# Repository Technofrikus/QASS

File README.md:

# QASS

QAZ-like for a BAE (Big Ass Enter) and 10u spacebar (7u+8u)

More pictures and infos at [Moinboards](https://moinboards.de/projects/qass/).
[Buildguide](https://moinboards.de/guides/guide-qass/).

There are three versions: normal, lowbar (Miao for FAK-Firmware) and lowbar (Gemini for QMK/Vial). The normal version has the spacebar on the normal PCB. The lowbar uses the PCB as a plate on the bottom row and adds a lower PCB.

- Only the lowbar version was tested and fully finished. Please check the normal version before ordering.
- Lowbar:
  - v1.0 is tested and works with MIAO. XIAO would work as well but the pads on the underside I wanted to use are not GPIOs but only for a special serial protocol. So they cant be used.
  - v1.1 is Untested, but I only made cosmetic changes, so should still work fine.
  - Quark-Works made a fork and changed the MCU to a [Gemini](https://keeb.supply/products/0xcb-gemini) (rp2040 zero compatible). Thanks! You can find it [here](https://github.com/quark-works/QASS-Zero/tree/main).
  - v1.2 Used the fork by Quarks as a basis. Removed a little mistake and made some cosmetic changes.
  - v1.3 the prvious version works, but the silkscreen of the diodes is not visible (orientation of diodes). Corrected this and changed the direction of one diode to be more consistent with the other ones around it.

The latest version has the lower spacebar. Break off the lower part of the PCB and put it under the bottom row. Add headers at the connection points.

## Case

The 3D-printable case files are included now (March 2025).
Can recommend making the plate from metal. Gives the build more weight and looks nice. Tested with brass and copper. Use the special version to make sure they will not warp during cutting (havent tested it without these, just a precaution).
Print recommendations included, see txt file. 

It is for the low-bar version only.

## Firmware
- FAK config and info can be found on [moinboards](https://moinboards.de/guides/guide-qass/#firmware-and-flashing) and here in the firmware folder.
- Vial/Qmk for the fork by Quark. Confirmed working.

## BOM

- [Miao MCU](https://keeb.supply/products/miao) (or [Gemini](https://keeb.supply/products/0xcb-gemini), if you use the Gemini-PCB
- 3mm high hotswap headers (2.54mm pitch) and pins (the holes in the PCB are bigger than usual, so only the plastic part of the headers is on the PCB)
- 20x BAV70 diodes

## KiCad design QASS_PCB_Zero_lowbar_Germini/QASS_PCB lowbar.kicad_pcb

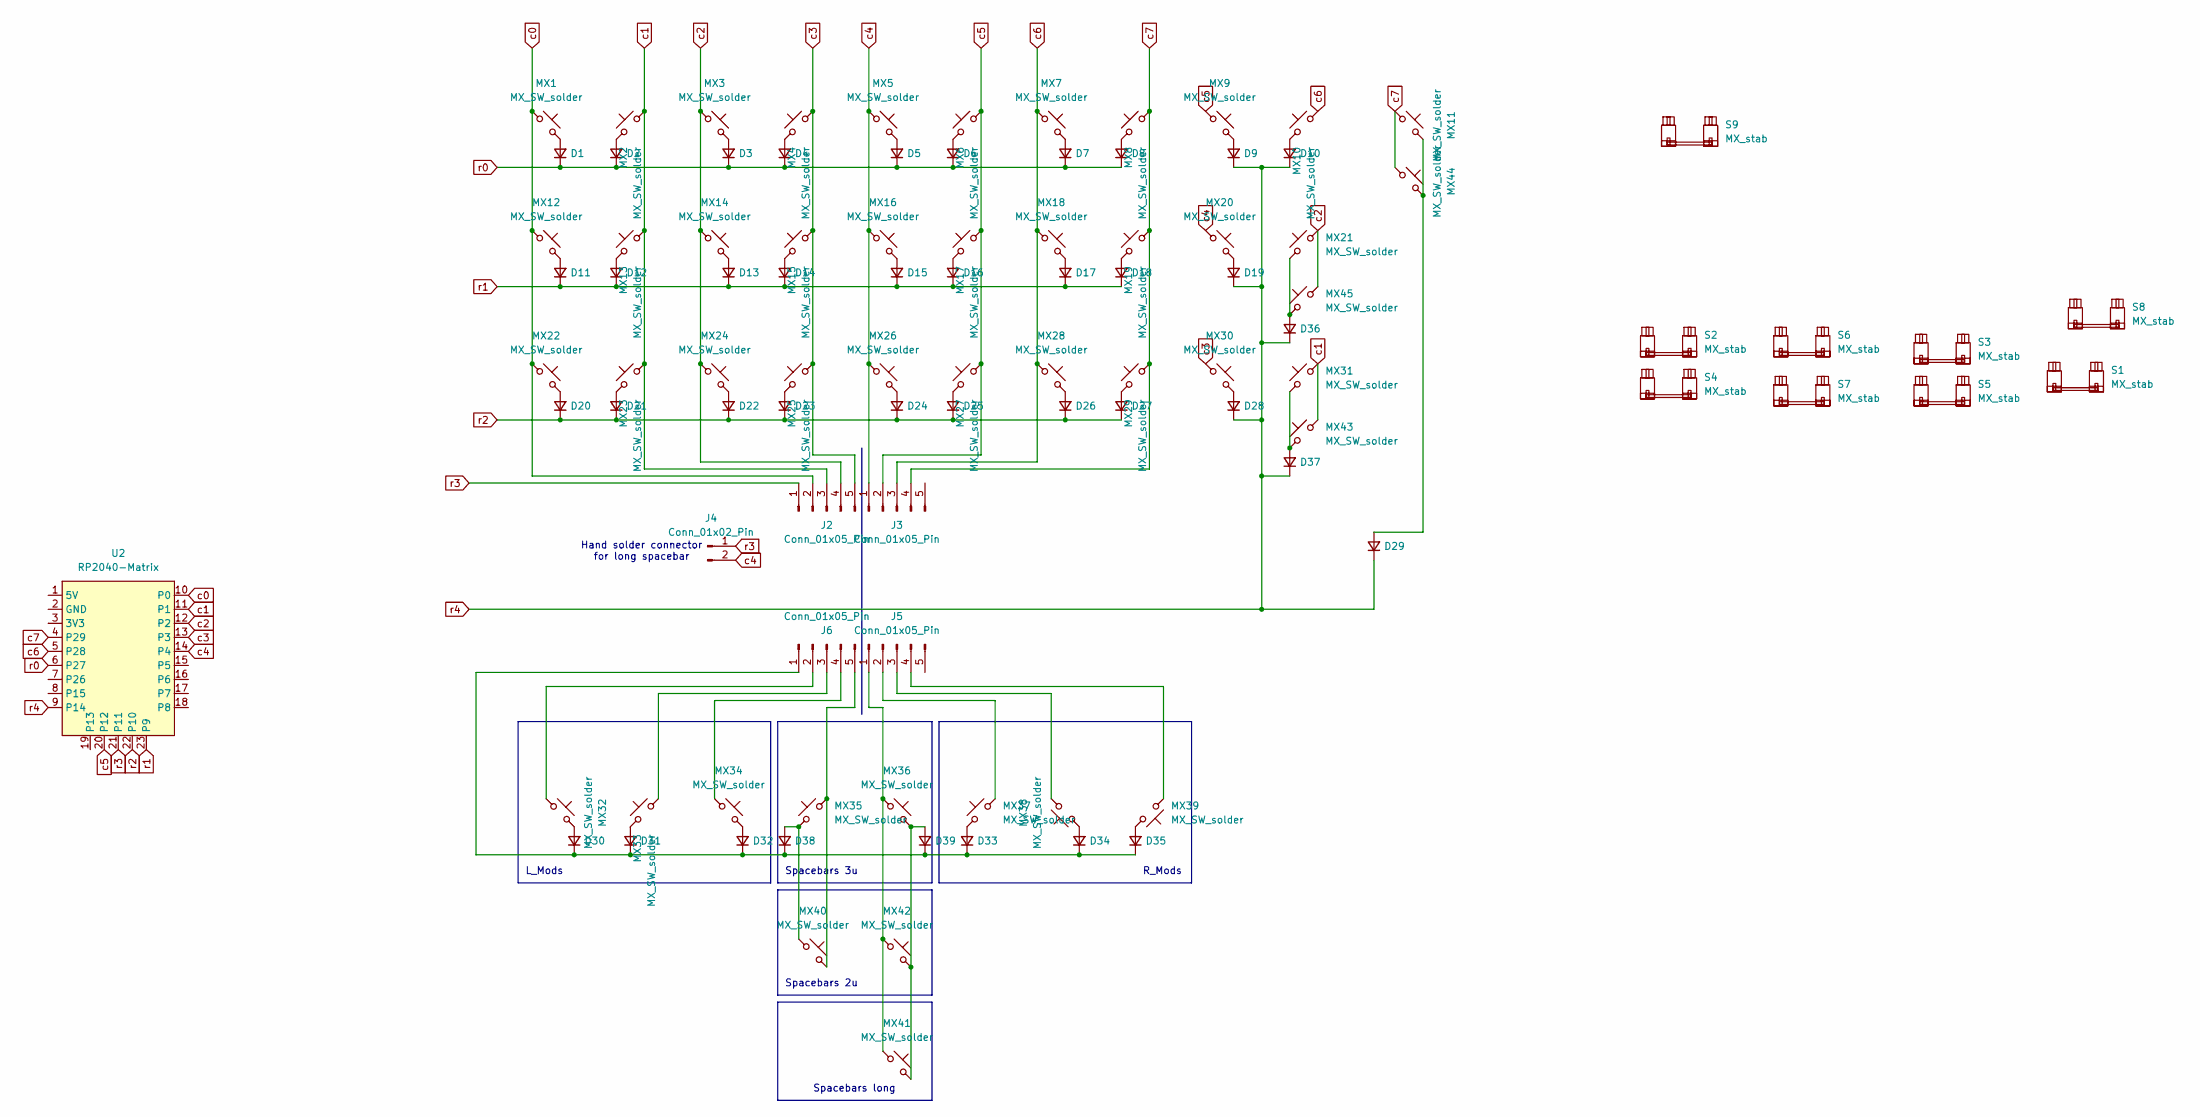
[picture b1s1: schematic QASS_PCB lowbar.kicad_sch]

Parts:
D1, D2, D3, D4, D5, D6, D7, D8, D9, D10, D11, D12, D13, D14, D15, D16, D17, D18, D19, D20, D21, D22, D23, D24, D25, D26, D27, D28, D29, D30, D31, D32, D33, D34, D35, D36, D37, D38, D39: 1n4148; Diode-dual
J2, J3, J5, J6: Conn_01x05_Pin; PinHeader_1x05_P2.54mm_Vertical
J4: Conn_01x02_Pin; PinHeader_1x02_P2.54mm_Vertical
MX1, MX2, MX3, MX4, MX5, MX6, MX7, MX8, MX9, MX10, MX13, MX14, MX15, MX16, MX17, MX18, MX19, MX20, MX21, MX23, MX24, MX25, MX26, MX27, MX28, MX29, MX30, MX32, MX33, MX34, MX35, MX36, MX37, MX38, MX39, MX40, MX41, MX42, MX43, MX45: MX_SW_solder; SW_MX_1u
MX11, MX44: MX_SW_solder; SW_MX_1.5u
MX12: MX_SW_solder; SW_MX_1.25u
MX22, MX31: MX_SW_solder; SW_MX_1.75u
S1: MX_stab; STAB_MX_2.25u
S2, S3: MX_stab; STAB_MX_3u
S4, S5: MX_stab; STAB_MX_2u
S6: MX_stab; STAB_MX_P_6u
S7: MX_stab; STAB_MX_P_10u
S8: MX_stab; STAB_MX_2.75u
S9: MX_stab; STAB_MX_P_ISO
U2: RP2040-Matrix; RP2040-Matrix_AH

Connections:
unnamed: D1.2 (A), MX1.2
unnamed: D2.2 (A), MX2.2
unnamed: D3.2 (A), MX3.2
unnamed: D4.2 (A), MX4.2
unnamed: D5.2 (A), MX5.2
unnamed: D6.2 (A), MX6.2
unnamed: D7.2 (A), MX7.2
unnamed: D8.2 (A), MX8.2
unnamed: D9.2 (A), MX9.2
unnamed: D10.2 (A), MX10.2
unnamed: D11.2 (A), MX12.2
unnamed: D12.2 (A), MX13.2
unnamed: D13.2 (A), MX14.2
unnamed: D14.2 (A), MX15.2
unnamed: D15.2 (A), MX16.2
unnamed: D16.2 (A), MX17.2
unnamed: D17.2 (A), MX18.2
unnamed: D18.2 (A), MX19.2
unnamed: D19.2 (A), MX20.2
unnamed: D20.2 (A), MX22.2
unnamed: D21.2 (A), MX23.2
unnamed: D22.2 (A), MX24.2
unnamed: D23.2 (A), MX25.2
unnamed: D24.2 (A), MX26.2
unnamed: D25.2 (A), MX27.2
unnamed: D26.2 (A), MX28.2
unnamed: D27.2 (A), MX29.2
unnamed: D28.2 (A), MX30.2
unnamed: D29.2 (A), MX11.1, MX44.1
unnamed: D30.2 (A), MX32.1
unnamed: D30.1 (K), D31.1 (K), D32.1 (K), D33.1 (K), D34.1 (K), D35.1 (K), D38.1 (K), D39.1 (K), J6.1
unnamed: D31.2 (A), MX33.2
unnamed: D32.2 (A), MX34.2
unnamed: D33.2 (A), MX37.1
unnamed: D34.2 (A), MX38.2
unnamed: D35.2 (A), MX39.2
unnamed: D36.2 (A), MX21.1, MX45.1
unnamed: D37.2 (A), MX31.1, MX43.1
unnamed: D38.2 (A), MX35.1, MX40.1
unnamed: D39.2 (A), MX36.2, MX41.2, MX42.2
unnamed: J5.1, MX36.1, MX41.1, MX42.1
unnamed: J5.2, MX37.2
unnamed: J5.3, MX38.1
unnamed: J5.4, MX39.1
unnamed: J6.2, MX32.2
unnamed: J6.3, MX33.1
unnamed: J6.4, MX34.1
unnamed: J6.5, MX35.2, MX40.2
c0: J2.2, MX1.1, MX12.1, MX22.1, U2.10 (P0)
c1: J2.3, MX2.1, MX13.1, MX23.1, MX31.2, MX43.2, U2.11 (P1)
c2: J2.4, MX3.1, MX14.1, MX21.2, MX24.1, MX45.2, U2.12 (P2)
c3: J2.5, MX4.1, MX15.1, MX25.1, MX30.1, U2.13 (P3)
c4: J3.1, J4.2, MX5.1, MX16.1, MX20.1, MX26.1, U2.14 (P4)
c5: J3.2, MX6.1, MX9.1, MX17.1, MX27.1, U2.20 (P12)
c6: J3.3, MX7.1, MX10.1, MX18.1, MX28.1, U2.5 (P28)
c7: J3.4, MX8.1, MX11.2, MX19.1, MX29.1, MX44.2, U2.4 (P29)
r0: D1.1 (K), D2.1 (K), D3.1 (K), D4.1 (K), D5.1 (K), D6.1 (K), D7.1 (K), D8.1 (K), U2.6 (P27)
r1: D11.1 (K), D12.1 (K), D13.1 (K), D14.1 (K), D15.1 (K), D16.1 (K), D17.1 (K), D18.1 (K), U2.23 (P9)
r2: D20.1 (K), D21.1 (K), D22.1 (K), D23.1 (K), D24.1 (K), D25.1 (K), D26.1 (K), D27.1 (K), U2.22 (P10)
r3: J2.1, J4.1, U2.21 (P11)
r4: D9.1 (K), D10.1 (K), D19.1 (K), D28.1 (K), D29.1 (K), D36.1 (K), D37.1 (K), U2.9 (P14)

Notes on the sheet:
Hand solder connector for long spacebar
L_Mods
R_Mods
Spacebars 2u
Spacebars 3u
Spacebars long

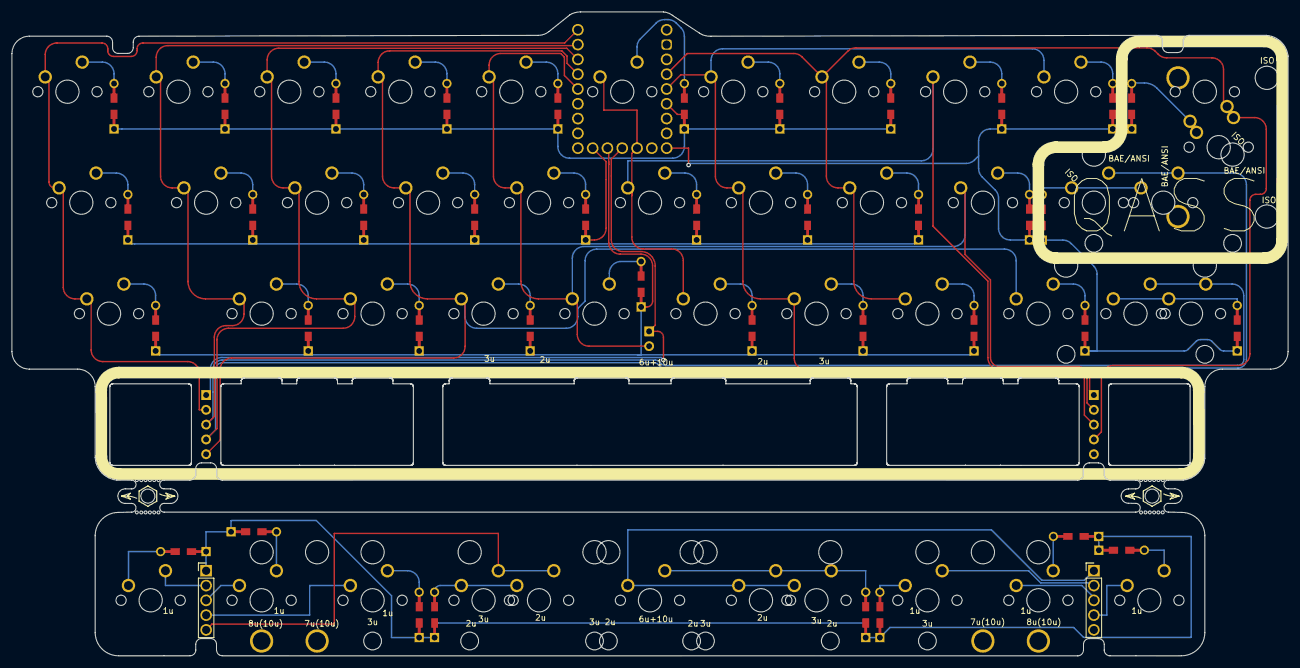
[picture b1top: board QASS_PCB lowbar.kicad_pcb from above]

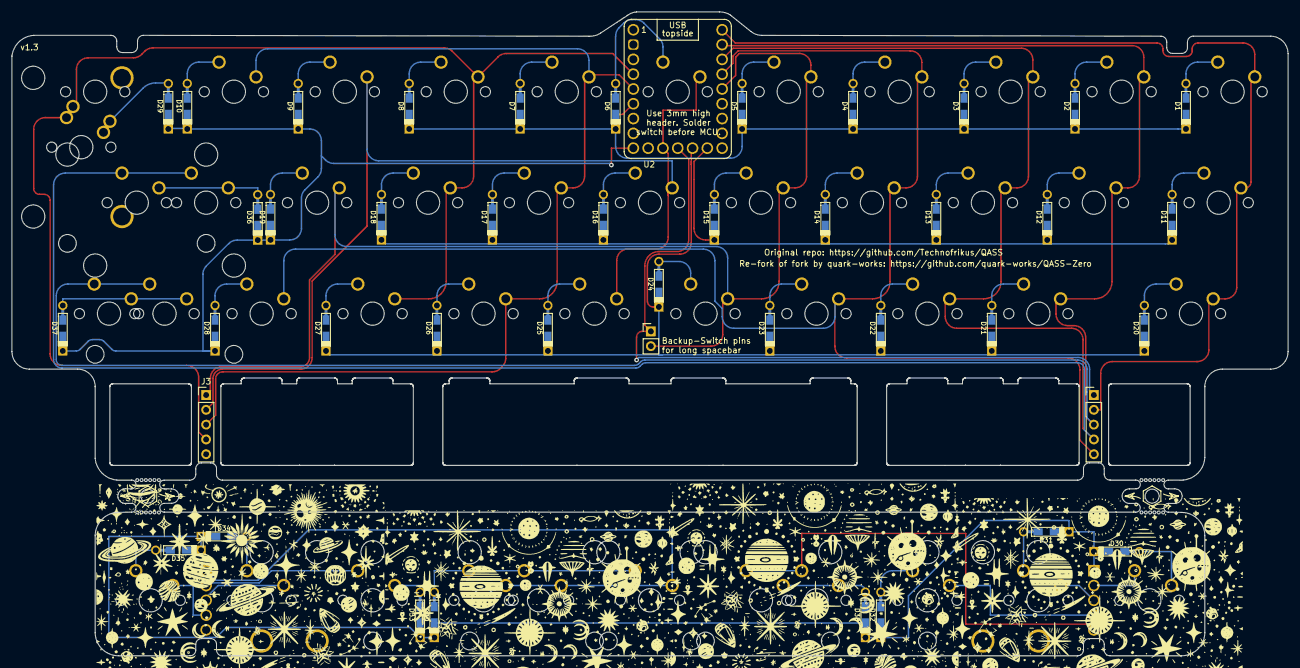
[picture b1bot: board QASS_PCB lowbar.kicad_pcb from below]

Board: 2 copper layers, 219.1 x 110.5 mm, 104 parts (47 on the bottom side), 61 nets.

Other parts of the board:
MB5, MB5#2: 5.5mm; mousebites_5p5mm_easysnap
Ref**: Val**; starpattern
Ref**#2, Ref**#3, Ref**#4: Val**; starpattern

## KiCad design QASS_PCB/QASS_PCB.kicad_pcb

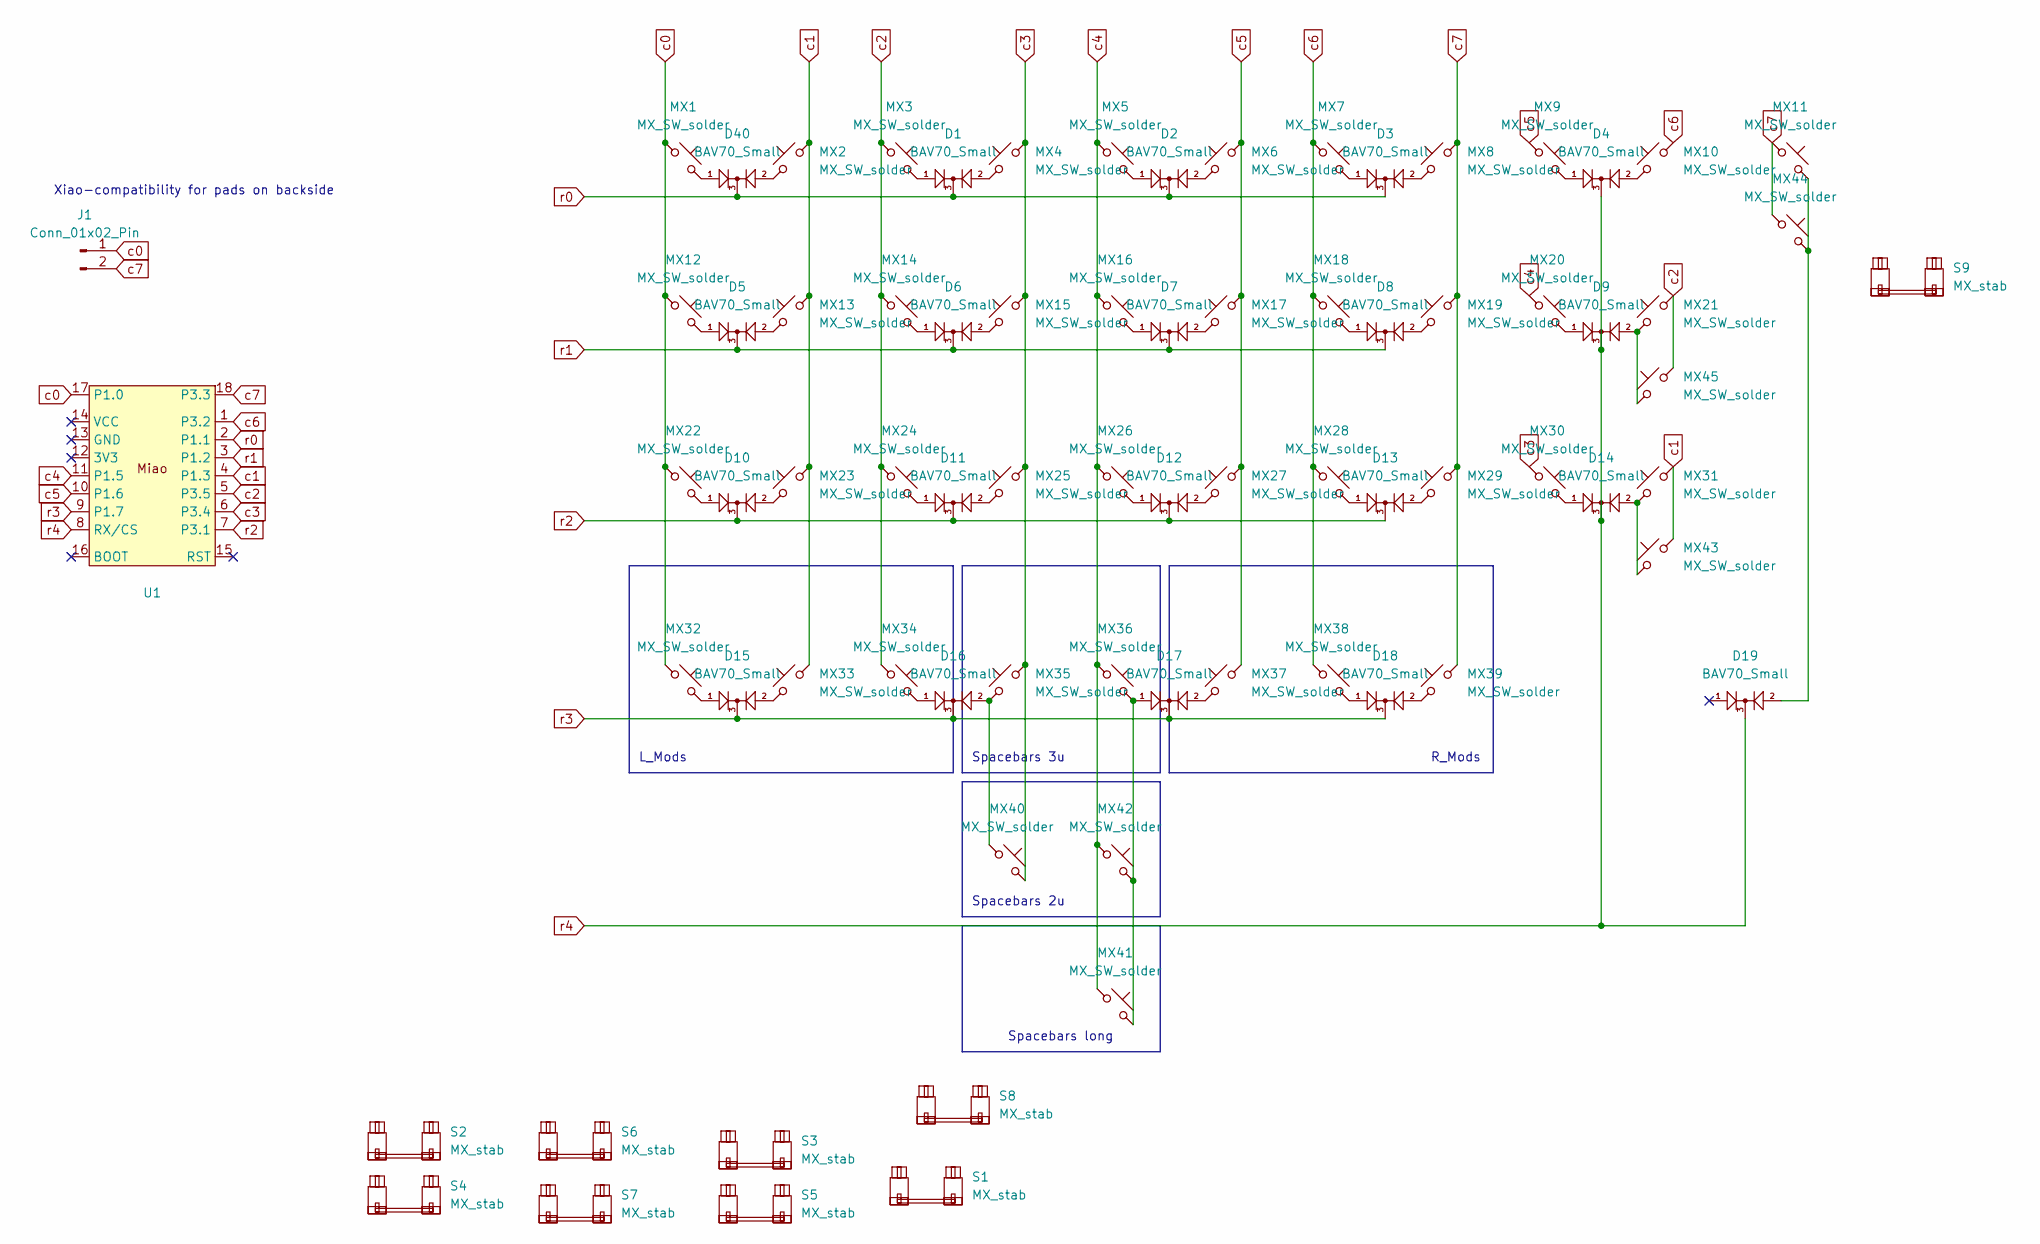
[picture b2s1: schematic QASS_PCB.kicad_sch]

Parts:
D1, D2, D3, D4, D5, D6, D7, D8, D9, D10, D11, D12, D13, D14, D15, D16, D17, D18, D19, D40: BAV70_Small; SOT-23
J1: Conn_01x02_Pin; PinHeader_1x02_P2.54mm_Vertical
MX1, MX2, MX3, MX4, MX5, MX6, MX7, MX8, MX9, MX10, MX13, MX14, MX15, MX16, MX17, MX18, MX19, MX20, MX21, MX23, MX24, MX25, MX26, MX27, MX28, MX29, MX30, MX32, MX33, MX34, MX35, MX36, MX37, MX38, MX39, MX40, MX41, MX42, MX43, MX45: MX_SW_solder; SW_MX_1u
MX11, MX44: MX_SW_solder; SW_MX_1.5u
MX12: MX_SW_solder; SW_MX_1.25u
MX22, MX31: MX_SW_solder; SW_MX_1.75u
S1: MX_stab; STAB_MX_2.25u
S2, S3: MX_stab; STAB_MX_3u
S4, S5: MX_stab; STAB_MX_2u
S6: MX_stab; STAB_MX_P_6u
S7: MX_stab; STAB_MX_P_10u
S8: MX_stab; STAB_MX_2.75u
S9: MX_stab; STAB_MX_P_ISO
U1: Miao

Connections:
unnamed: D1.1 (A1), MX3.2
unnamed: D1.2 (A2), MX4.1
unnamed: D2.1 (A1), MX5.2
unnamed: D2.2 (A2), MX6.1
unnamed: D3.1 (A1), MX7.2
unnamed: D3.2 (A2), MX8.1
unnamed: D4.1 (A1), MX9.2
unnamed: D4.2 (A2), MX10.1
unnamed: D5.1 (A1), MX12.2
unnamed: D5.2 (A2), MX13.1
unnamed: D6.1 (A1), MX14.2
unnamed: D6.2 (A2), MX15.1
unnamed: D7.1 (A1), MX16.2
unnamed: D7.2 (A2), MX17.1
unnamed: D8.1 (A1), MX18.2
unnamed: D8.2 (A2), MX19.1
unnamed: D9.1 (A1), MX20.2
unnamed: D9.2 (A2), MX21.1, MX45.1
unnamed: D10.1 (A1), MX22.2
unnamed: D10.2 (A2), MX23.1
unnamed: D11.1 (A1), MX24.2
unnamed: D11.2 (A2), MX25.1
unnamed: D12.1 (A1), MX26.2
unnamed: D12.2 (A2), MX27.1
unnamed: D13.1 (A1), MX28.2
unnamed: D13.2 (A2), MX29.1
unnamed: D14.1 (A1), MX30.2
unnamed: D14.2 (A2), MX31.1, MX43.1
unnamed: D15.1 (A1), MX32.2
unnamed: D15.2 (A2), MX33.1
unnamed: D16.1 (A1), MX34.2
unnamed: D16.2 (A2), MX35.1, MX40.1
unnamed: D17.1 (A1), MX36.2, MX41.2, MX42.2
unnamed: D17.2 (A2), MX37.1
unnamed: D18.1 (A1), MX38.2
unnamed: D18.2 (A2), MX39.1
unnamed: D19.2 (A2), MX11.2, MX44.2
unnamed: D40.1 (A1), MX1.2
unnamed: D40.2 (A2), MX2.1
c0: J1.1, MX1.1, MX12.1, MX22.1, MX32.1, U1.17 (P1.0)
c1: MX2.2, MX13.2, MX23.2, MX31.2, MX33.2, MX43.2, U1.4 (P1.3)
c2: MX3.1, MX14.1, MX21.2, MX24.1, MX34.1, MX45.2, U1.5 (P3.5)
c3: MX4.2, MX15.2, MX25.2, MX30.1, MX35.2, MX40.2, U1.6 (P3.4)
c4: MX5.1, MX16.1, MX20.1, MX26.1, MX36.1, MX41.1, MX42.1, U1.11 (P1.5)
c5: MX6.2, MX9.1, MX17.2, MX27.2, MX37.2, U1.10 (P1.6)
c6: MX7.1, MX10.2, MX18.1, MX28.1, MX38.1, U1.1 (P3.2)
c7: J1.2, MX8.2, MX11.1, MX19.2, MX29.2, MX39.2, MX44.1, U1.18 (P3.3)
r0: D1.3 (K), D2.3 (K), D3.3 (K), D40.3 (K), U1.2 (P1.1)
r1: D5.3 (K), D6.3 (K), D7.3 (K), D8.3 (K), U1.3 (P1.2)
r2: D10.3 (K), D11.3 (K), D12.3 (K), D13.3 (K), U1.7 (P3.1)
r3: D15.3 (K), D16.3 (K), D17.3 (K), D18.3 (K), U1.9 (P1.7)
r4: D4.3 (K), D9.3 (K), D14.3 (K), D19.3 (K), U1.8 (RX/CS)

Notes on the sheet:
L_Mods
R_Mods
Spacebars 2u
Xiao-compatibility for pads on backside
Spacebars 3u
Spacebars long

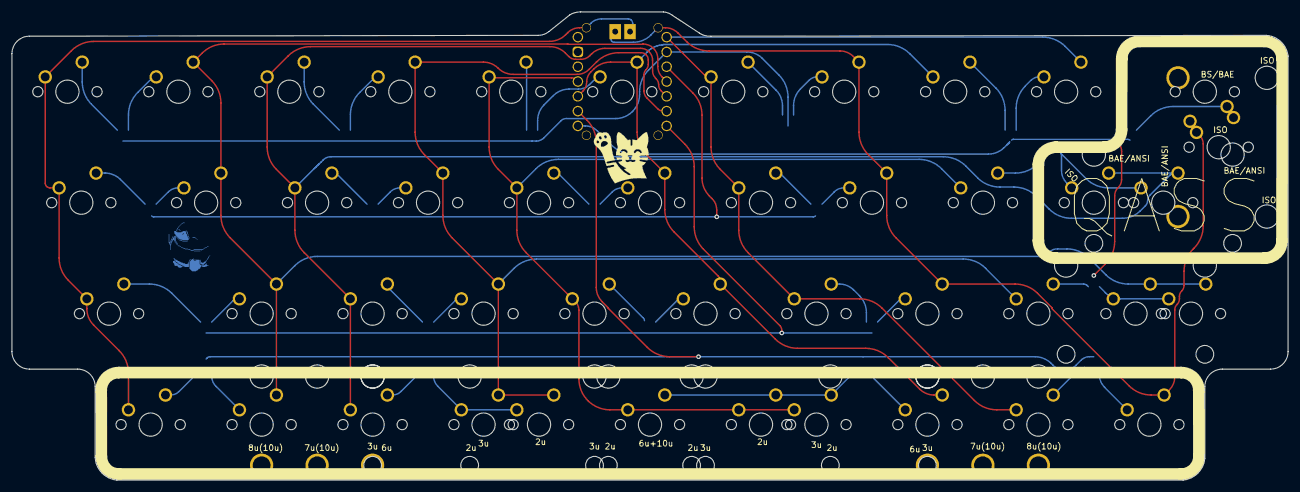
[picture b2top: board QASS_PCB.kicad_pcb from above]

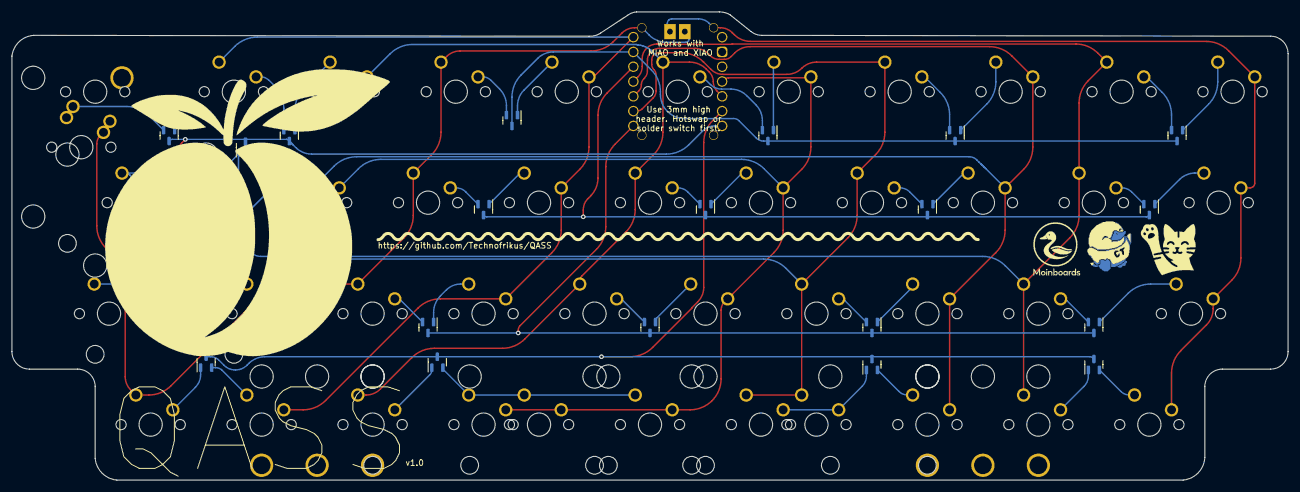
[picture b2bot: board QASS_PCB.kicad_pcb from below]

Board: 2 copper layers, 219.1 x 80.4 mm, 80 parts (25 on the bottom side), 52 nets.

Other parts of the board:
Ref**: Val**; Miaoxiao 10mm
Ref**#2: Val**; Miaoxiao 10mm
Ref**#3: Val**; Duck 2 with text
Ref**#4: Val**; peach simple qass logo

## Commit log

2024-02-21 Add .gitignore
2024-02-21 Erster Runde
2024-02-24 working on it
2024-02-24 Routing down, pretty close to final
2024-02-25 Step exported
2024-02-25 Create license
2024-02-25 move license
2024-02-25 KLE update
2024-02-25 Added 2.75u right shift option
2024-02-25 Updated KLE with 2.75 shift
2024-02-29 Added ISO Enter
2024-03-10 Second version added: lowbar
2024-03-16 v1.0, protoype ordered
2024-05-03 v1.1 - [x] Beschriftung der Switches in der BottomRow auf Oberem PCB - [x] Doppelten 6+3u stab entfert - [x] Switchpositionen auf unterem PCB auch markiert - [x] Unteren zwei Löcher für MCU weggelass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
2024-05-03 Added renders of lowbar PCB
2024-05-18 Update README.md with new and correct pictures
2024-05-18 Updated KLE
2024-05-18 KLE update again
2025-03-22 Added Case
2025-03-28 Added Link to the fork of the PCB with Gemini MCU
2025-03-28 Added the fork of the PCB with Gemini MCU
2026-01-31 Added Firmware files for FAK and VIAL (for fork by Quark)
2026-01-31 Used the fork by Quarks to make my own Gemini-Version of the PCB. A small mistake was fixed and some asthetic changes made.
2026-03-01 PCB lowbar for Gemini finished. Ordered. Untested yet.
2026-03-15 v1.3 - silkscreen better and one diode orientation more consistent
2026-03-15 correct version number in Silk
2026-03-29 Added Custom Bottom Row Keys for printing
